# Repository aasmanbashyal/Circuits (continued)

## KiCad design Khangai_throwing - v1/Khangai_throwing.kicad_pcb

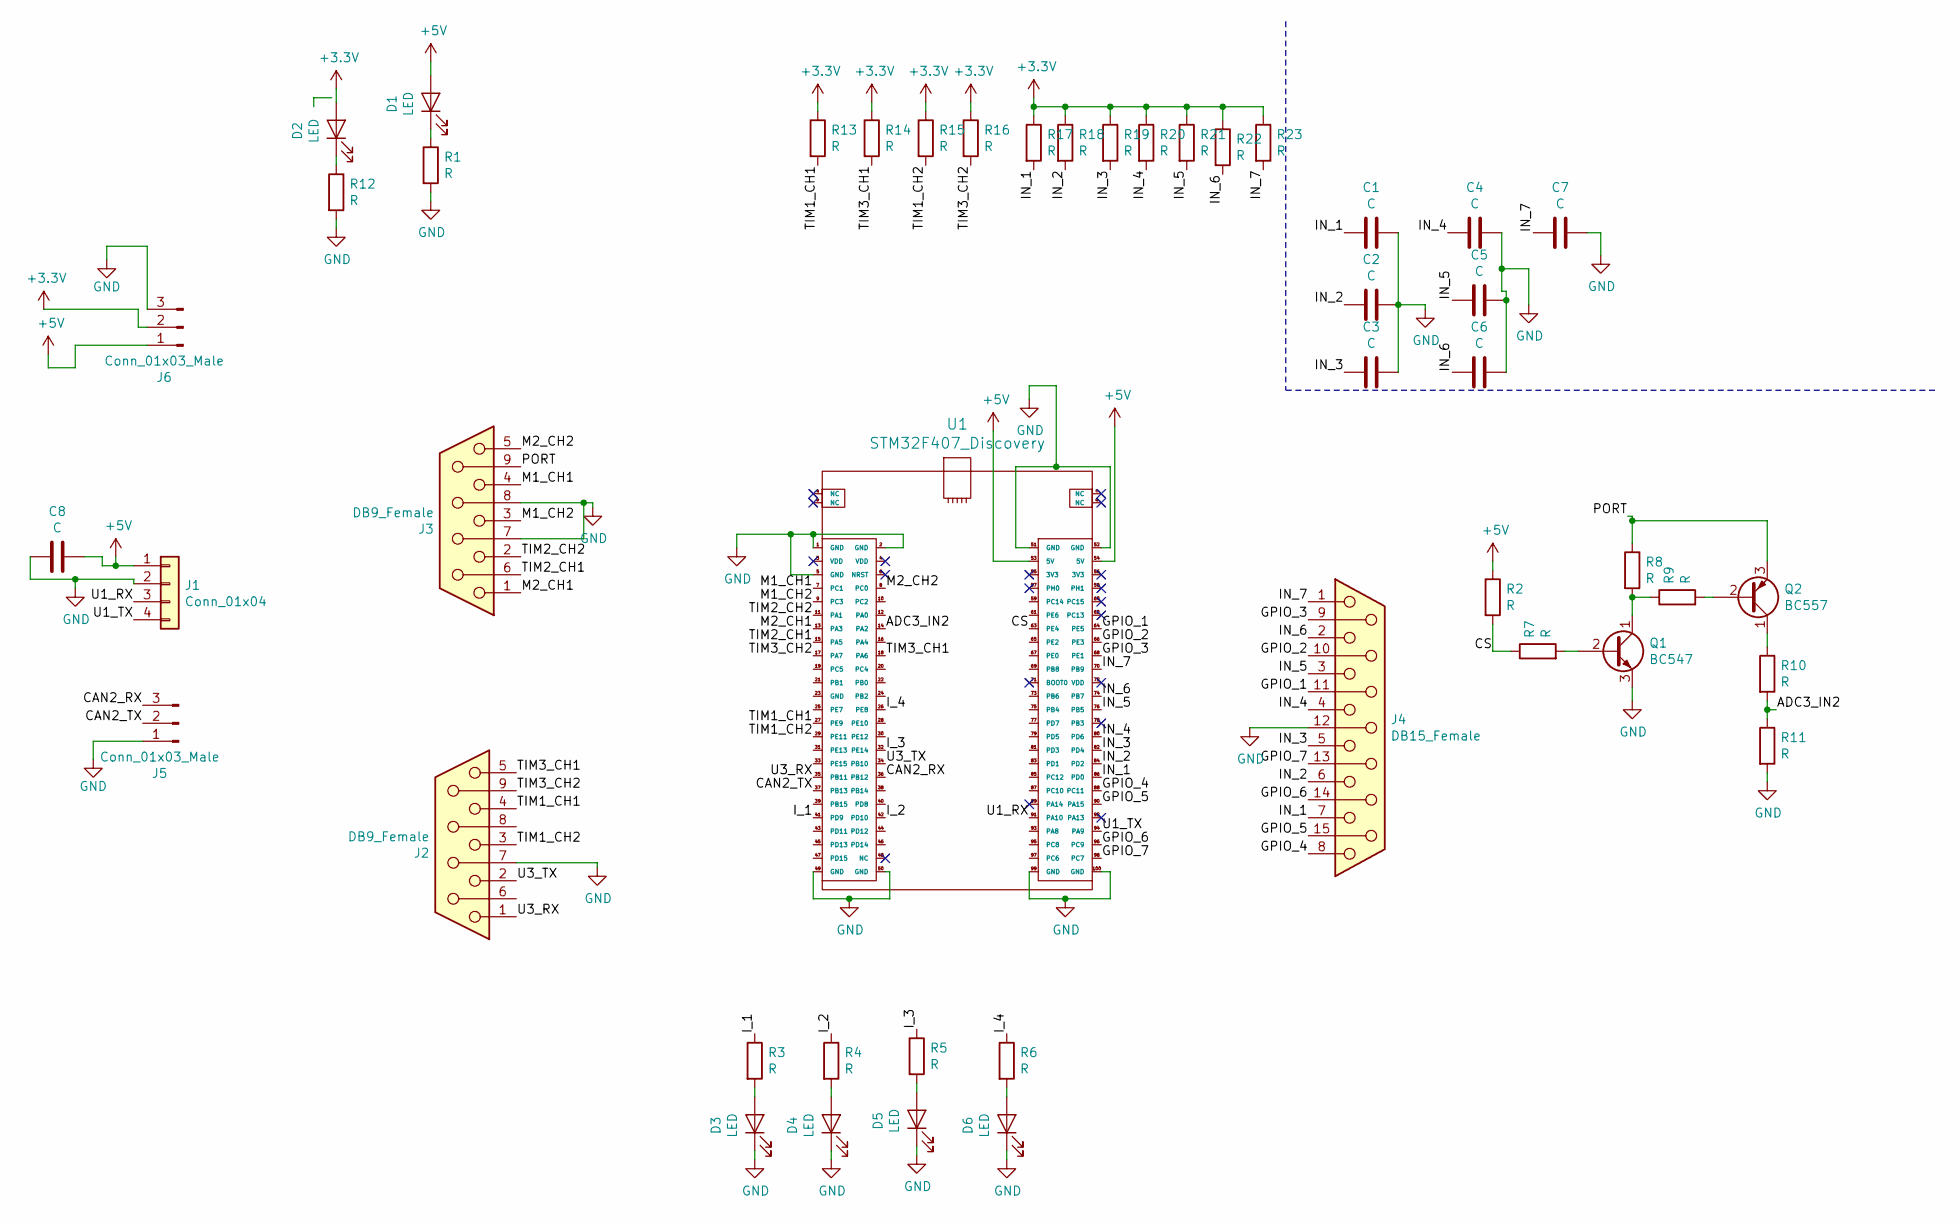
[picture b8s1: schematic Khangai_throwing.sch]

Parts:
C1, C2, C3, C4, C5, C6, C7, C8: C; Capacitor_Disc_Small
D1, D2, D3, D4, D5, D6: LED; LED_D3.0mm
J1: Conn_01x04; Pin_Header_Straight_1x04_Pitch2.54mm
J2, J3: DB9_Female; Connector_DB_9
J4: DB15_Female; Connector_DB15
J5: Conn_01x03_Male; Connector_Bornier_3
J6: Conn_01x03_Male; Large_Connector_Bornier_3
Q1: BC547
Q2: BC557; BC547
R1, R2, R3, R4, R5, R6, R7, R8, R9, R10, R11, R12, R13, R14, R15, R16, R17, R18, R19, R20, R21, R22, R23: R; Resistor_small
U1: STM32F407_Discovery

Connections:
+3V3: D2.2 (A), J6.2, R13.1, R14.1, R15.1, R16.1, R17.1, R18.1, R19.1, R20.1, R21.1, R22.1, R23.1
+5V: C8.1, D1.2 (A), J1.1, J6.1, R2.1, U1.53 (5V), U1.54 (5V)
/ADC3_IN2: R10.2, R11.1, U1.14 (PA2)
/CAN2_RX: J5.3, U1.36 (PB12)
/CAN2_TX: J5.2, U1.37 (PB13)
/CS: R2.2, R7.1, U1.63 (PE4)
/GPIO_1: J4.11 (P111), U1.64 (PE5)
/GPIO_2: J4.10, U1.66 (PE3)
/GPIO_3: J4.9, U1.68 (PE1)
/GPIO_4: J4.8, U1.88 (PC11)
/GPIO_5: J4.15, U1.90 (PA15)
/GPIO_6: J4.14, U1.96 (PC9)
/GPIO_7: J4.13, U1.98 (PC7)
/IN_1: C1.2, J4.7, R17.2, U1.86 (PD0)
/IN_2: C2.2, J4.6, R18.2, U1.84 (PD2)
/IN_3: C3.2, J4.5, R19.2, U1.82 (PD4)
/IN_4: C4.2, J4.4, R20.2, U1.80 (PD6)
/IN_5: C5.2, J4.3, R21.2, U1.76 (PB5)
/IN_6: C6.2, J4.2, R22.2, U1.74 (PB7)
/IN_7: C7.2, J4.1, R23.2, U1.70 (PB9)
/I_1: R3.1, U1.41 (PD9)
/I_2: R4.1, U1.42 (PD10)
/I_3: R5.1, U1.32 (PE14)
/I_4: R6.1, U1.26 (PE8)
/M1_CH1: J3.4, U1.7 (PC1)
/M1_CH2: J3.3, U1.9 (PC3)
/M2_CH1: J3.1, U1.13 (PA3)
/M2_CH2: J3.5, U1.8 (PC0)
/PORT: J3.9, Q2.3 (E), R8.1
/TIM1_CH1: J2.4, R13.2, U1.27 (PE9)
/TIM1_CH2: J2.3, R15.2, U1.29 (PE11)
/TIM2_CH1: J3.6, U1.15 (PA5)
/TIM2_CH2: J3.2, U1.11 (PA1)
/TIM3_CH1: J2.5, R14.2, U1.18 (PA6)
/TIM3_CH2: J2.9, R16.2, U1.17 (PA7)
/U1_RX: J1.3, U1.91 (PA10)
/U1_TX: J1.4, U1.94 (PA9)
/U3_RX: J2.1, U1.35 (PB11)
/U3_TX: J2.2, U1.34 (PB10)
GND: C1.1, C2.1, C3.1, C4.1, C5.1, C6.1, C7.1, C8.2, D3.1 (K), D4.1 (K), D5.1 (K), D6.1 (K), J1.2, J2.7, J3.7, J3.8, J4.12, J5.1, J6.3, Q1.3 (E), R1.2, R11.2, R12.2, U1.1 (GND), U1.2 (GND), U1.5 (GND), U1.49 (GND), U1.50 (GND), U1.51 (GND), U1.52 (GND), U1.99 (GND), U1.100 (GND)
unnamed: D1.1 (K), R1.1
unnamed: D2.1 (K), R12.1
unnamed: D3.2 (A), R3.2
unnamed: D4.2 (A), R4.2
unnamed: D5.2 (A), R5.2
unnamed: D6.2 (A), R6.2
unnamed: Q1.1 (C), R8.2, R9.1
unnamed: Q1.2 (B), R7.2
unnamed: Q2.1 (C), R10.1
unnamed: Q2.2 (B), R9.2

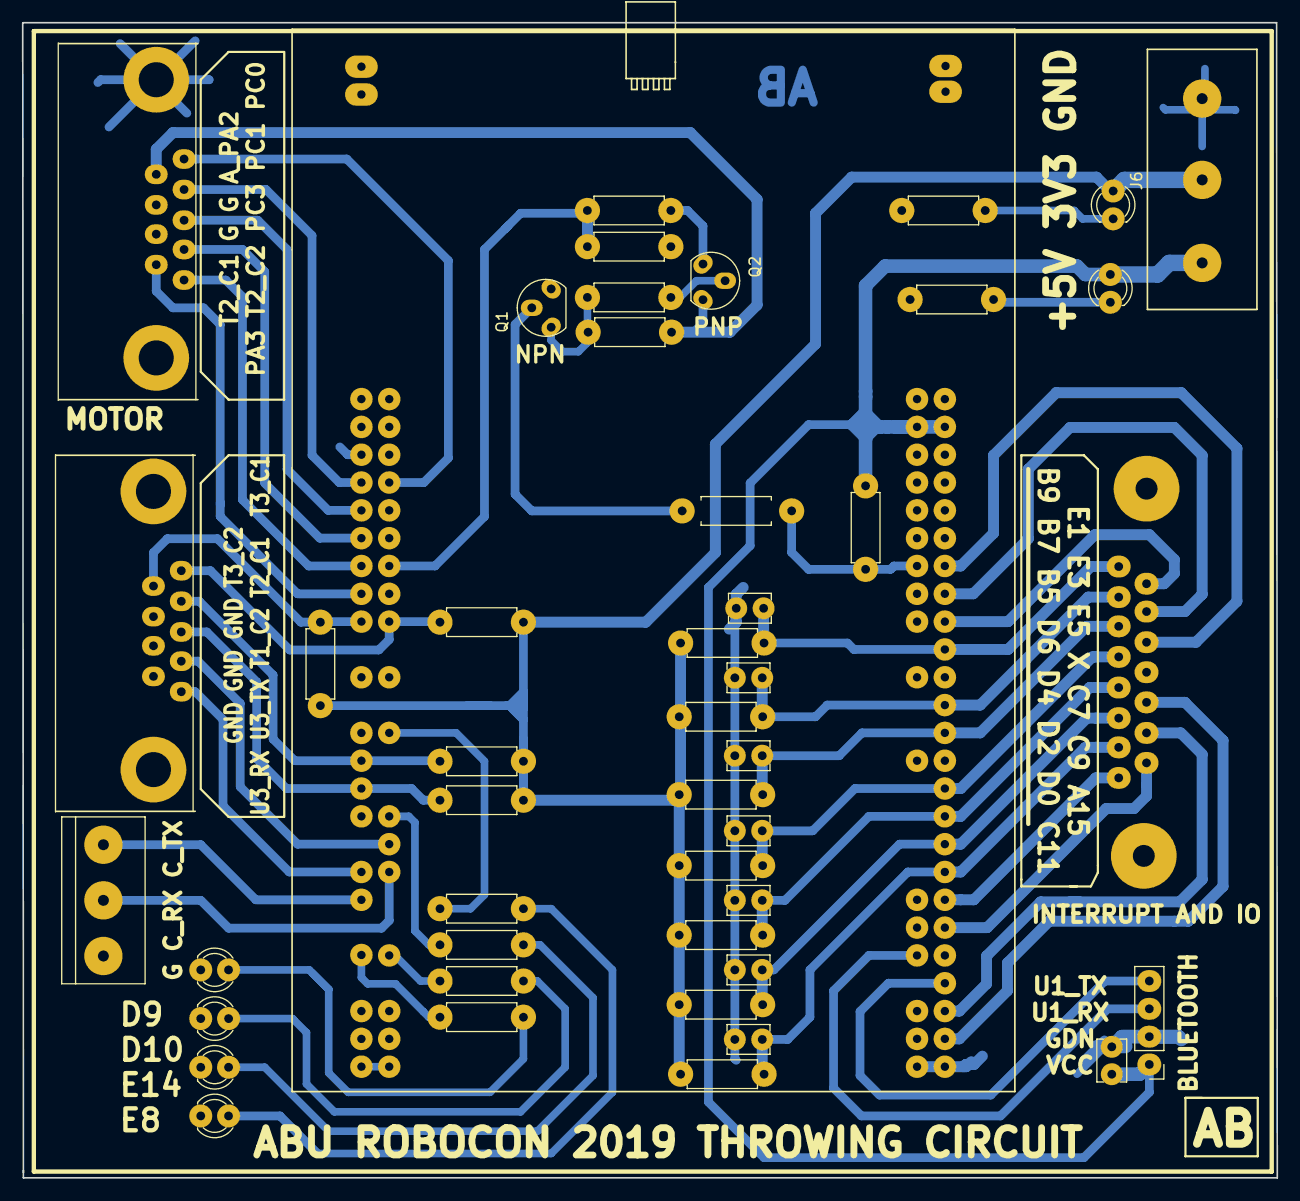
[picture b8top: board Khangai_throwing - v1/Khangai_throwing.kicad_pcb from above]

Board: 2 copper layers, 114.6 x 105.5 mm, 46 parts (0 on the bottom side), 50 nets.

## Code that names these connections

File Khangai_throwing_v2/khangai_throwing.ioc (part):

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Mcu.Name=STM32F407V(E-G)Tx
Mcu.Package=LQFP100
Mcu.UserName=STM32F407VGTx
PA1.Signal=S_TIM2_CH2
PA10.Mode=Asynchronous
PA10.Signal=USART1_RX
PA15.Signal=GPIO_Output
PA3.Signal=GPIO_Output
PA5.Signal=S_TIM2_CH1_ETR
PA6.Signal=S_TIM3_CH1
PA7.Signal=S_TIM3_CH2
PA9.Mode=Asynchronous
PA9.Signal=USART1_TX
PB10.Mode=Asynchronous
PB10.Signal=USART3_TX
PB11.Mode=Asynchronous
PB11.Signal=USART3_RX
PB5.Signal=GPXTI5
PB7.Signal=GPXTI7
PB9.Signal=GPXTI9
PC0.Signal=GPIO_Output
PC1.Signal=GPIO_Output
PC11.Signal=GPIO_Output
PC3.Signal=GPIO_Output
PC7.Signal=GPIO_Output
PC9.Signal=GPIO_Output
PD10.Signal=GPIO_Output
PD2.Signal=GPXTI2
PD9.Signal=GPIO_Output
PE1.Signal=GPIO_Output
PE11.Signal=S_TIM1_CH2
PE14.Signal=GPIO_Output
PE3.Signal=GPIO_Output
PE5.Signal=GPIO_Output
PE8.Signal=GPIO_Output
PE9.Signal=S_TIM1_CH1
PH0-OSC_IN.Mode=HSE-External-Oscillator
PH0-OSC_IN.Signal=RCC_OSC_IN
PH1-OSC_OUT.Mode=HSE-External-Oscillator
PH1-OSC_OUT.Signal=RCC_OSC_OUT
RCC.HSE_VALUE=25000000
RCC.SYSCLKFreq_VALUE=16000000
board=custom

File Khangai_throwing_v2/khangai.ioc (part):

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Mcu.Name=STM32F407V(E-G)Tx
Mcu.Package=LQFP100
Mcu.UserName=STM32F407VGTx
PA0-WKUP.Signal=GPIO_Output
PA1.Signal=S_TIM2_CH2
PA10.Mode=Asynchronous
PA10.Signal=USART1_RX
PA13.Mode=Trace_Asynchronous_SW
PA13.Signal=SYS_JTMS-SWDIO
PA14.Mode=Trace_Asynchronous_SW
PA14.Signal=SYS_JTCK-SWCLK
PA2.Signal=ADCx_IN2
PA3.Signal=GPIO_Output
PA5.Signal=S_TIM2_CH1_ETR
PA6.Signal=S_TIM3_CH1
PA7.Signal=S_TIM3_CH2
PA9.Mode=Asynchronous
PA9.Signal=USART1_TX
PB1.Signal=GPIO_Output
PB10.Mode=Asynchronous
PB10.Signal=USART3_TX
PB11.Mode=Asynchronous
PB11.Signal=USART3_RX
PB12.Mode=Slave
PB12.Signal=CAN2_RX
PB13.Mode=Slave
PB13.Signal=CAN2_TX
PB3.Mode=Trace_Asynchronous_SW
PB3.Signal=SYS_JTDO-SWO
PB5.Signal=GPXTI5
PB6.Signal=S_TIM4_CH1
PB7.Signal=GPXTI7
PB8.Signal=S_TIM4_CH3
PB9.Signal=GPXTI9
PC0.Signal=GPIO_Output
PC1.Signal=GPIO_Output
PC14-OSC32_IN.Mode=LSE-External-Oscillator
PC14-OSC32_IN.Signal=RCC_OSC32_IN
PC15-OSC32_OUT.Mode=LSE-External-Oscillator
PC15-OSC32_OUT.Signal=RCC_OSC32_OUT
PC2.Signal=GPIO_Output
PC3.Signal=GPIO_Output
PC6.Signal=GPIO_Output
PC7.Signal=GPIO_Output
PD0.Signal=GPXTI0
PD12.Signal=GPIO_Output
PD13.Signal=GPIO_Output
PD14.Signal=GPIO_Output
PD15.Signal=GPIO_Output
PD4.Signal=GPXTI4
PD6.Signal=GPXTI6
PE11.Signal=S_TIM1_CH2
PE4.Signal=GPIO_Output
PE9.Signal=S_TIM1_CH1
PH0-OSC_IN.Mode=HSE-External-Oscillator
PH0-OSC_IN.Signal=RCC_OSC_IN
PH1-OSC_OUT.Mode=HSE-External-Oscillator
PH1-OSC_OUT.Signal=RCC_OSC_OUT
RCC.HSE_VALUE=25000000
RCC.SYSCLKFreq_VALUE=16000000
board=custom
